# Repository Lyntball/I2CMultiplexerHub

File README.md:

# I2CMultiplexerHub
I2C Multiplexer Hub Sor Sensor Reading and Device Control

This is a hub for reading data from sensors with the same address or controlling devices with the same address. The inital creation was to read multiple sensors with the same I2C address. After exploring the possibilities, I was able to use the same structure as TCP/IP to use the multiplexer as a 'sub-net' of sorts

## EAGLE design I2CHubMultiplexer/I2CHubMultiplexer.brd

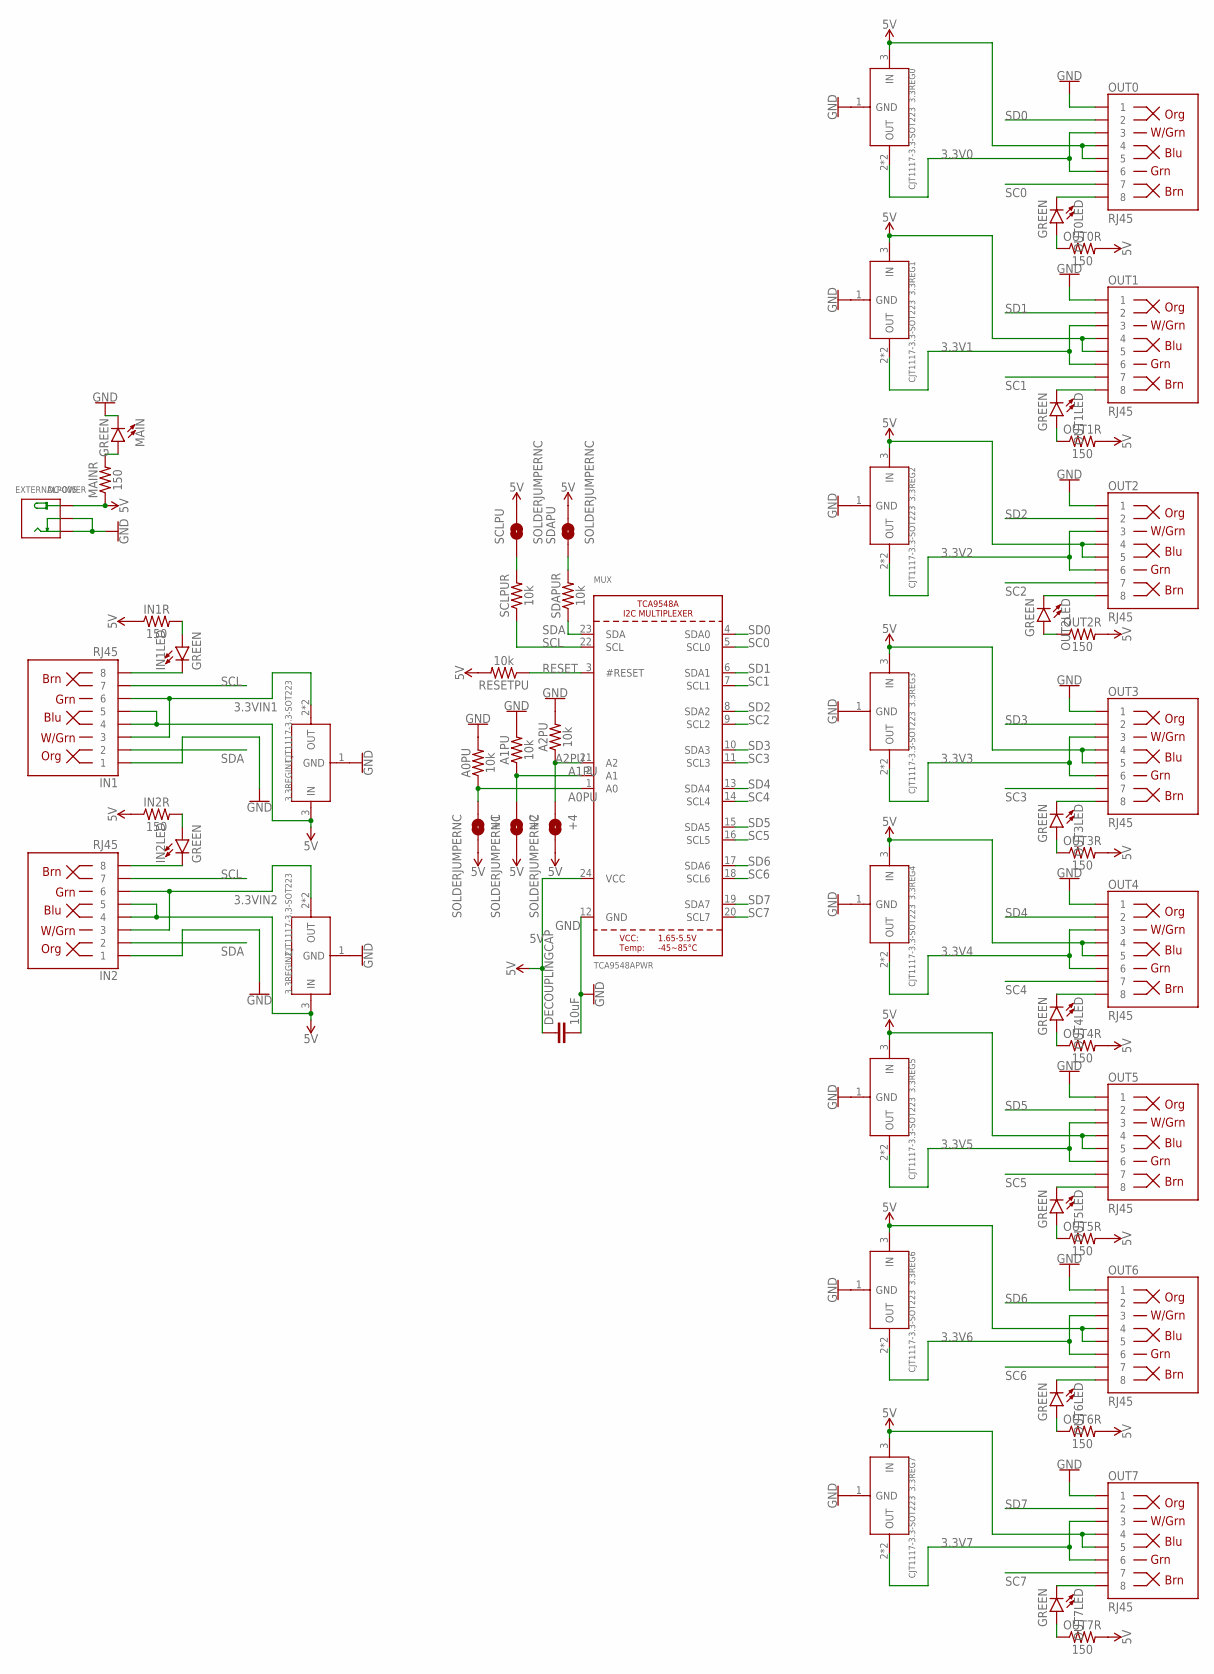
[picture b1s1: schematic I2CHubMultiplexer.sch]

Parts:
3.3REG0, 3.3REG1, 3.3REG2, 3.3REG3, 3.3REG4, 3.3REG5, 3.3REG6, 3.3REG7, 3.3REGIN1, 3.3REGIN2: CJT1117-3.3-SOT223; SOT-223
+1, +2, +4: SOLDERJUMPERNC; SJ_2S
A0PU, A1PU, A2PU: 10k; 0603
DECOUPLINGCAP: 10uF; 0603
EXTERNALPOWER: DC-005; DCJ3P-14.2X11.0X9.0MM
IN1, IN2: RJ45; RJ45-8
IN1LED, IN2LED: GREEN; LED-0603
IN1R, IN2R: 150; 0603
MAIN: GREEN; LED-0603
MAINR: 150; 0603
MUX: TCA9548APWR; TSSOP24
OUT0, OUT1, OUT2, OUT3, OUT4, OUT5, OUT6, OUT7: RJ45; RJ45-8
OUT0LED, OUT1LED, OUT2LED, OUT3LED, OUT4LED, OUT5LED, OUT6LED, OUT7LED: GREEN; LED-0603
OUT0R, OUT1R, OUT2R, OUT3R, OUT4R, OUT5R, OUT6R, OUT7R: 150; 0603
RESETPU: 10k; 0603
SCLPU: SOLDERJUMPERNC; SJ_2S
SCLPUR: 10k; 0603
SDAPU: SOLDERJUMPERNC; SJ_2S
SDAPUR: 10k; 0603

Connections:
3.3V0: 3.3REG0.2 (OUT), 3.3REG0.TER (OUT), OUT0.3, OUT0.6
3.3V1: 3.3REG1.2 (OUT), 3.3REG1.TER (OUT), OUT1.3, OUT1.6
3.3V2: 3.3REG2.2 (OUT), 3.3REG2.TER (OUT), OUT2.3, OUT2.6
3.3V3: 3.3REG3.2 (OUT), 3.3REG3.TER (OUT), OUT3.3, OUT3.6
3.3V4: 3.3REG4.2 (OUT), 3.3REG4.TER (OUT), OUT4.3, OUT4.6
3.3V5: 3.3REG5.2 (OUT), 3.3REG5.TER (OUT), OUT5.3, OUT5.6
3.3V6: 3.3REG6.2 (OUT), 3.3REG6.TER (OUT), OUT6.3, OUT6.6
3.3V7: 3.3REG7.2 (OUT), 3.3REG7.TER (OUT), OUT7.3, OUT7.6
3.3VIN1: 3.3REGIN1.2 (OUT), 3.3REGIN1.TER (OUT), IN1.3, IN1.6
3.3VIN2: 3.3REGIN2.2 (OUT), 3.3REGIN2.TER (OUT), IN2.3, IN2.6
5V: 3.3REG0.3 (IN), 3.3REG1.3 (IN), 3.3REG2.3 (IN), 3.3REG3.3 (IN), 3.3REG4.3 (IN), 3.3REG5.3 (IN), 3.3REG6.3 (IN), 3.3REG7.3 (IN), 3.3REGIN1.3 (IN), 3.3REGIN2.3 (IN), +1.2, +2.2, +4.2, DECOUPLINGCAP.1, EXTERNALPOWER.+, IN1.4, IN1.5, IN1R.1, IN2.4, IN2.5, IN2R.1, MAINR.1, MUX.24 (VCC), OUT0.4, OUT0.5, OUT0R.2, OUT1.4, OUT1.5, OUT1R.2, OUT2.4, OUT2.5, OUT2R.2, OUT3.4, OUT3.5, OUT3R.2, OUT4.4, OUT4.5, OUT4R.2, OUT5.4, OUT5.5, OUT5R.2, OUT6.4, OUT6.5, OUT6R.2, OUT7.4, OUT7.5, OUT7R.2, RESETPU.2, SCLPU.2, SDAPU.2
A0PU: +1.1, A0PU.1, MUX.1 (A0)
A1PU: +2.1, A1PU.1, MUX.2 (A1)
A2PU: +4.1, A2PU.1, MUX.21 (A2)
GND: 3.3REG0.1 (GND), 3.3REG1.1 (GND), 3.3REG2.1 (GND), 3.3REG3.1 (GND), 3.3REG4.1 (GND), 3.3REG5.1 (GND), 3.3REG6.1 (GND), 3.3REG7.1 (GND), 3.3REGIN1.1 (GND), 3.3REGIN2.1 (GND), A0PU.2, A1PU.2, A2PU.2, DECOUPLINGCAP.2, EXTERNALPOWER.-1 (-), EXTERNALPOWER.-2 (CDN), IN1.1, IN2.1, MAIN.C, MUX.12 (GND), OUT0.1, OUT1.1, OUT2.1, OUT3.1, OUT4.1, OUT5.1, OUT6.1, OUT7.1
IN1LEDR: IN1LED.A, IN1R.2
IN2LEDR: IN2LED.A, IN2R.2
MAINLEDR: MAIN.A, MAINR.2
OU1LEDR: OUT1LED.A, OUT1R.1
OUT0LEDR: OUT0LED.A, OUT0R.1
OUT2LEDR: OUT2LED.A, OUT2R.1
OUT3LEDR: OUT3LED.A, OUT3R.1
OUT4LEDR: OUT4LED.A, OUT4R.1
OUT5LEDR: OUT5LED.A, OUT5R.1
OUT6LEDR: OUT6LED.A, OUT6R.1
OUT7LEDR: OUT7LED.A, OUT7R.1
RESET: MUX.3 (#RESET), RESETPU.1
RETRUNGNDIN1: IN1.8, IN1LED.C
RETURNGNDIN2: IN2.8, IN2LED.C
RETURNGNDOUT1: OUT1.8, OUT1LED.C
RETURNGNDOUT2: OUT2.8, OUT2LED.C
RETURNGNDOUT3: OUT3.8, OUT3LED.C
RETURNGNDOUT4: OUT4.8, OUT4LED.C
RETURNGNDOUT5: OUT5.8, OUT5LED.C
RETURNGNDOUT6: OUT6.8, OUT6LED.C
RETURNGNDOUT7: OUT7.8, OUT7LED.C
RETURNGRNDOUT0: OUT0.8, OUT0LED.C
SC0: MUX.5 (SCL0), OUT0.7
SC1: MUX.7 (SCL1), OUT1.7
SC2: MUX.9 (SCL2), OUT2.7
SC3: MUX.11 (SCL3), OUT3.7
SC4: MUX.14 (SCL4), OUT4.7
SC5: MUX.16 (SCL5), OUT5.7
SC6: MUX.18 (SCL6), OUT6.7
SC7: MUX.20 (SCL7), OUT7.7
SCL: IN1.7, IN2.7, MUX.22 (SCL), SCLPUR.1
SCLPU: SCLPU.1, SCLPUR.2
SD0: MUX.4 (SDA0), OUT0.2
SD1: MUX.6 (SDA1), OUT1.2
SD2: MUX.8 (SDA2), OUT2.2
SD3: MUX.10 (SDA3), OUT3.2
SD4: MUX.13 (SDA4), OUT4.2
SD5: MUX.15 (SDA5), OUT5.2
SD6: MUX.17 (SDA6), OUT6.2
SD7: MUX.19 (SDA7), OUT7.2
SDA: IN1.2, IN2.2, MUX.23 (SDA), SDAPUR.1
SDAPU: SDAPU.1, SDAPUR.2

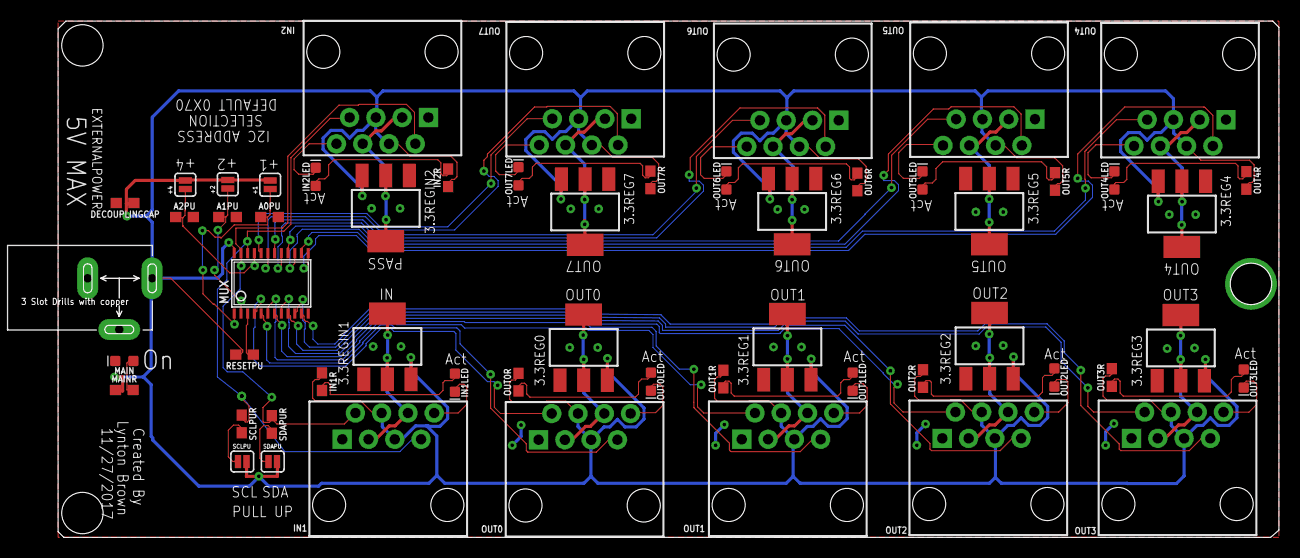
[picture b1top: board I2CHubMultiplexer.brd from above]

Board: 2 copper layers, 121.5 x 49.8 mm, 56 parts (0 on the bottom side), 57 nets.

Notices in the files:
parts and their libraries:
SparkFun-Retired: Licensing: Creative Commons ShareAlike 4.0 International - https://creativecommons.org/licenses/by-sa/4.0
microbuilder: This work is placed in the public domain, and may be freely used for commercial and non-commercial work with the following conditions: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
